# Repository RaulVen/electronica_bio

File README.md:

# electronica_bio
bioreactor_V1

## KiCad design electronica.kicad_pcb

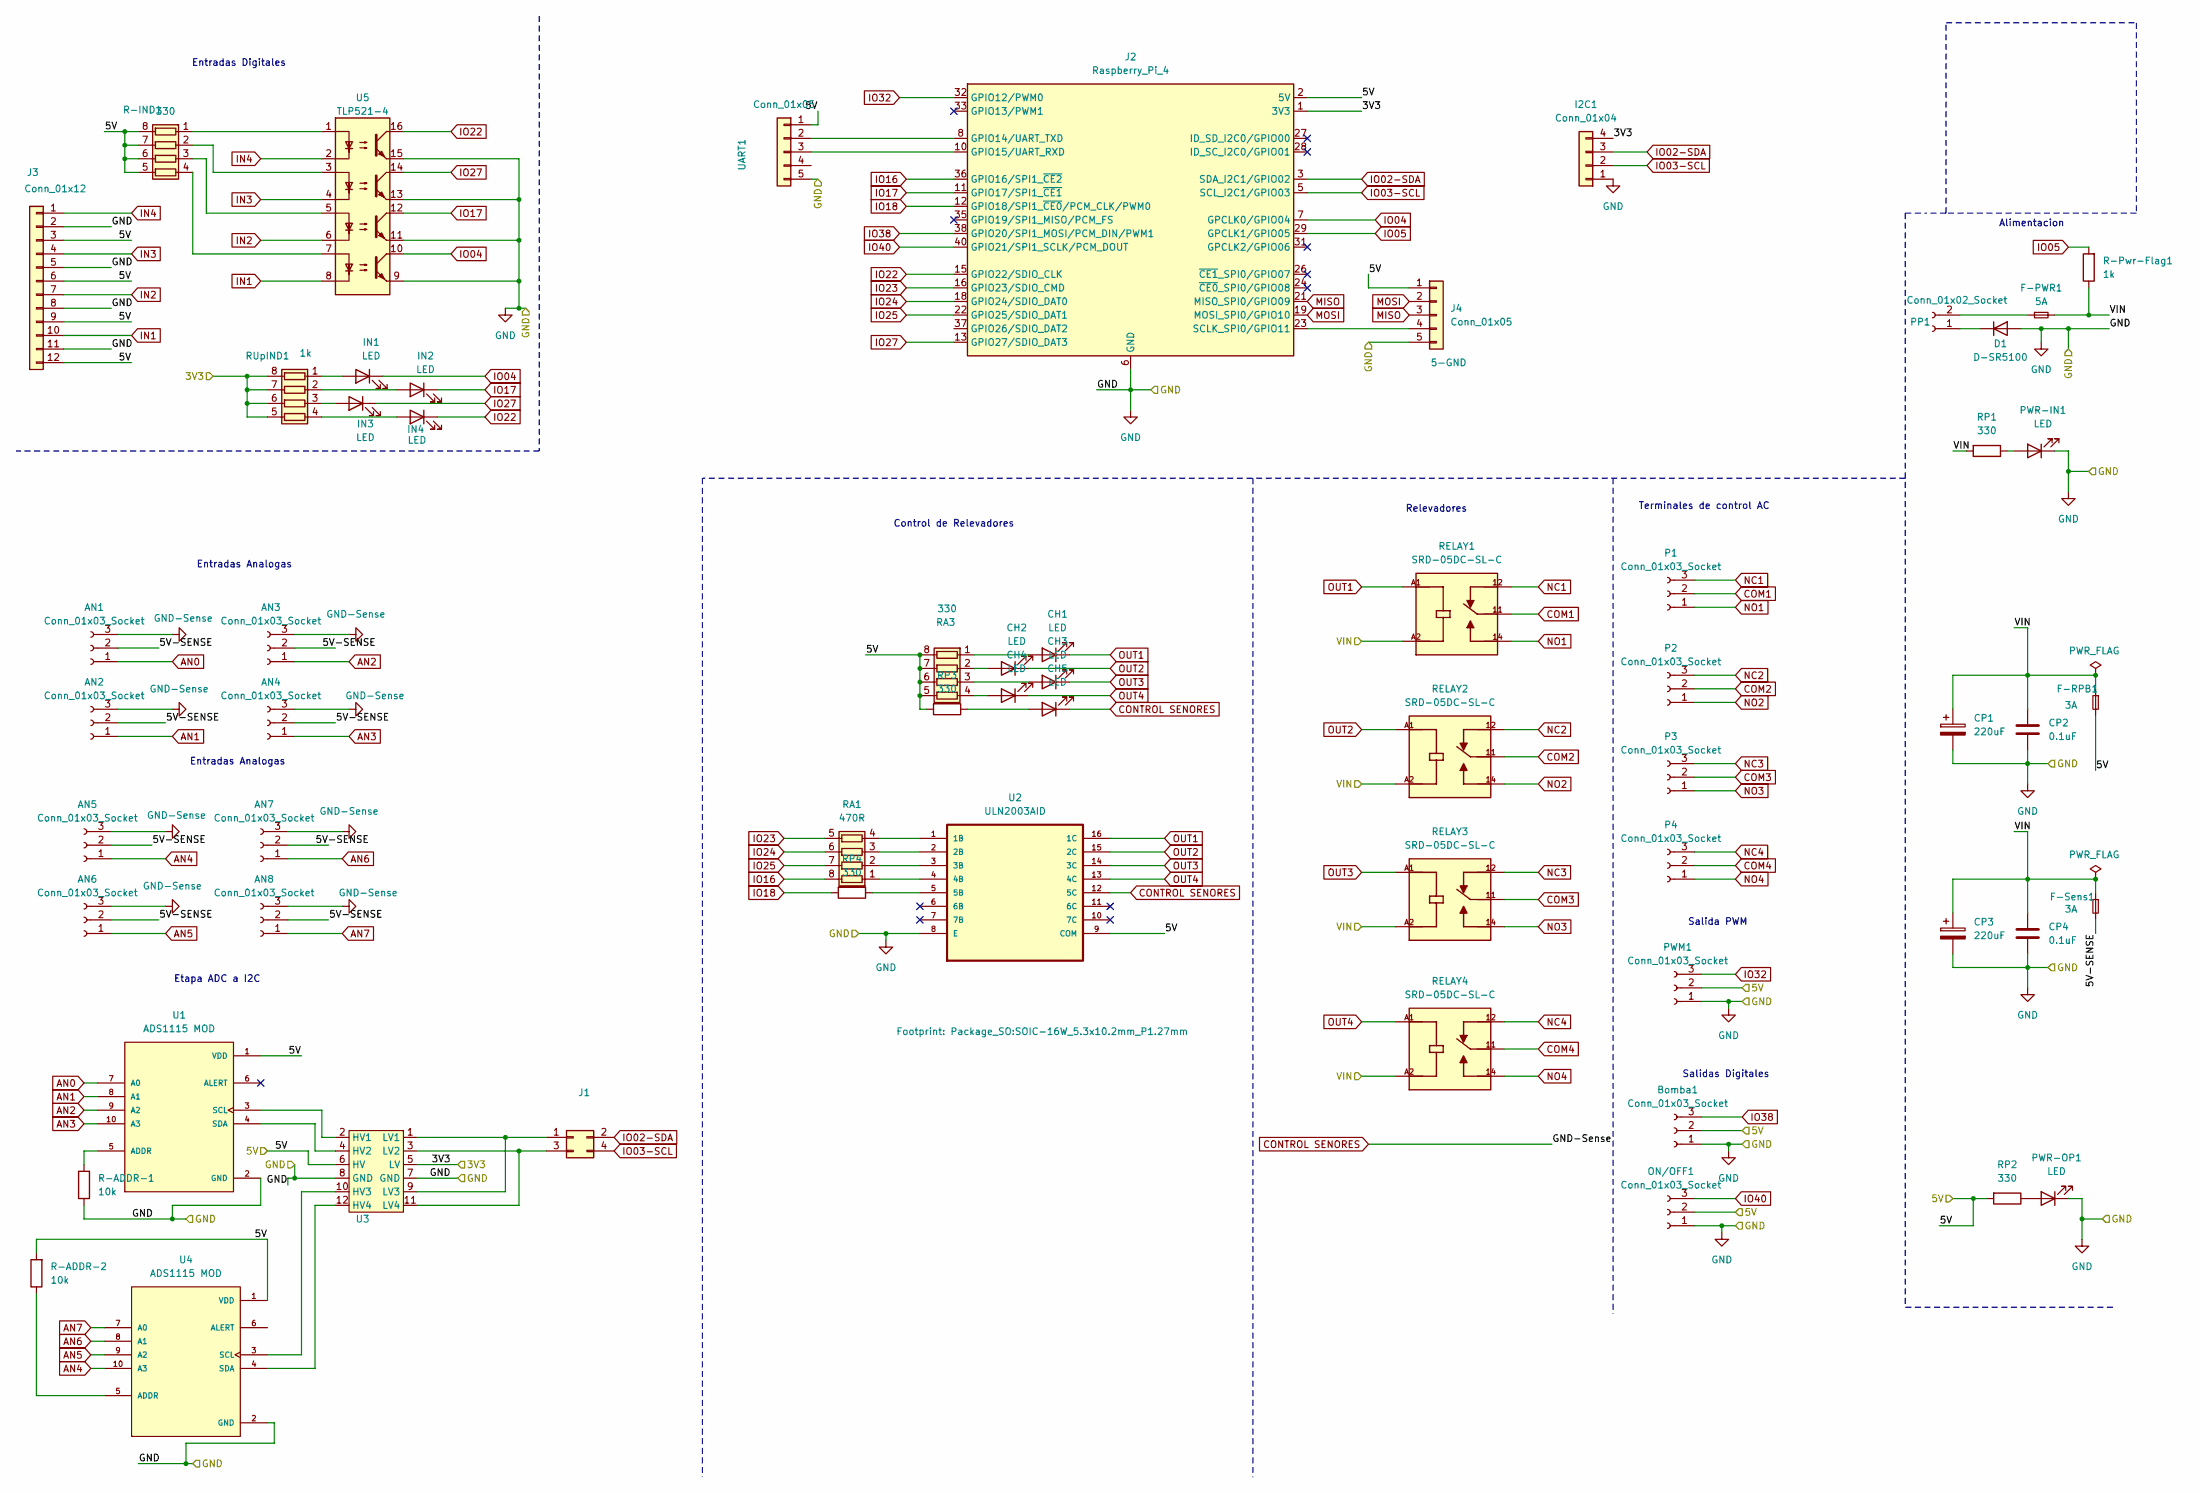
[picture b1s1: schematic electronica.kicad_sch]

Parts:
AN1, AN2, AN3, AN4, AN5, AN6, AN7, AN8: Conn_01x03_Socket; PinHeader_1x03_P2.54mm_Vertical
Bomba1: Conn_01x03_Socket; PinHeader_1x03_P2.54mm_Vertical
CH1, CH2, CH3, CH4, CH5: LED; LED_1206_3216Metric_Pad1.42x1.75mm_HandSolder
CP1, CP3: 220uF; CP_Radial_D8.0mm_P3.50mm
CP2, CP4: 0.1uF; C_1206_3216Metric
D1: D-SR5100; D_DO-41_SOD81_P7.62mm_Horizontal
F-PWR1: 5A; Fuse_1206_3216Metric
F-RPB1: 3A; Fuse_0603_1608Metric
F-Sens1: 3A; Fuse_0603_1608Metric
I2C1: Conn_01x04; PinHeader_1x04_P2.00mm_Vertical
IN1, IN2, IN3, IN4: LED; LED_1206_3216Metric_Pad1.42x1.75mm_HandSolder
J1: Conn_02x02_Counter_Clockwise; PinHeader_2x02_P2.54mm_Vertical
J2: Raspberry_Pi_4; Raspberry4-holes
J3: Conn_01x12; Samtec_HPM-12-05-x-S_Straight_1x12_Pitch5.08mm
J4: Conn_01x05; PinHeader_1x05_P2.00mm_Vertical
ON/OFF1: Conn_01x03_Socket; PinHeader_1x03_P2.54mm_Vertical
P1, P2, P3, P4: Conn_01x03_Socket; TerminalBlock_Phoenix_MKDS-1,5-3_1x03_P5.00mm_Horizontal
PP1: Conn_01x02_Socket; TerminalBlock_Phoenix_MKDS-1,5-2_1x02_P5.00mm_Horizontal
PWM1: Conn_01x03_Socket; PinHeader_1x03_P2.54mm_Vertical
PWR-IN1: LED; LED_1206_3216Metric_Pad1.42x1.75mm_HandSolder
PWR-OP1: LED; LED_1206_3216Metric_Pad1.42x1.75mm_HandSolder
R-ADDR-1, R-ADDR-2: 10k; R_1206_3216Metric_Pad1.30x1.75mm_HandSolder
R-IND1: 330; R_Array_Convex_4x1206
R-Pwr-Flag1: 1k; R_1206_3216Metric_Pad1.30x1.75mm_HandSolder
RA1: 470R; R_Array_Convex_4x1206
RA3: 330; R_Array_Convex_4x1206
RELAY1, RELAY2, RELAY3, RELAY4: SRD-05DC-SL-C; Relay_SPDT_Finder_36.11; PARTREV 1.0
RP1, RP2, RP3, RP4: 330; R_1206_3216Metric_Pad1.30x1.75mm_HandSolder
RUpIND1: 1k; R_Array_Convex_4x1206
U1, U4: ADS1115 MOD; ADS1115; PARTREV NA
U2: ULN2003AID; SOIC-16W_5.3x10.2mm_P1.27mm
U3: LVL Shifter
U5: TLP521-4; SOIC-16_4.55x10.3mm_P1.27mm
UART1: Conn_01x05; PinHeader_1x05_P2.00mm_Vertical

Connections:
/3V3: I2C1.4, J2.1 (3V3), J2.17 (3V3), RUpIND1.5 (R4.2), RUpIND1.6 (R3.2), RUpIND1.7 (R2.2), RUpIND1.8 (R1.2), U3.5 (LV)
/5V: Bomba1.2, F-RPB1.2, J2.2 (5V), J2.4 (5V), J3.3, J3.6, J3.9, J3.12, J4.1, ON/OFF1.2, PWM1.2, R-ADDR-2.2, R-IND1.5 (R4.2), R-IND1.6 (R3.2), R-IND1.7 (R2.2), R-IND1.8 (R1.2), RA3.5 (R4.2), RA3.6 (R3.2), RA3.7 (R2.2), RA3.8 (R1.2), RP2.2, RP3.2, U1.1 (VDD), U2.9 (COM), U3.6 (HV), U4.1 (VDD), UART1.1
/5V-SENSE: AN1.2, AN2.2, AN3.2, AN4.2, AN5.2, AN6.2, AN7.2, AN8.2, F-Sens1.2
/VIN: CP1.1, CP2.1, CP3.1, CP4.1, F-PWR1.2, F-RPB1.1, F-Sens1.1, R-Pwr-Flag1.1, RELAY1.A2, RELAY2.A2, RELAY3.A2, RELAY4.A2, RP1.2
AN0: AN1.1, U1.7 (A0)
AN1: AN2.1, U1.8 (A1)
AN2: AN3.1, U1.9 (A2)
AN3: AN4.1, U1.10 (A3)
AN4: AN5.1, U4.10 (A3)
AN5: AN6.1, U4.9 (A2)
AN6: AN7.1, U4.8 (A1)
AN7: AN8.1, U4.7 (A0)
COM1: P1.2, RELAY1.11
COM2: P2.2, RELAY2.11
COM3: P3.2, RELAY3.11
COM4: P4.2, RELAY4.11
CONTROL SENORES: AN1.3, AN2.3, AN3.3, AN4.3, AN5.3, AN6.3, AN7.3, AN8.3, CH5.1 (K), U2.12 (5C)
GND: Bomba1.1, CP1.2, CP2.2, CP3.2, CP4.2, D1.2 (A), I2C1.1, J2.6 (GND), J2.9 (GND), J2.14 (GND), J2.20 (GND), J2.25 (GND), J2.30 (GND), J2.34 (GND), J2.39 (GND), J3.2, J3.5, J3.8, J3.11, J4.5, ON/OFF1.1, PWM1.1, PWR-IN1.1 (K), PWR-OP1.1 (K), R-ADDR-1.1, U1.2 (GND), U2.8 (E), U3.7 (GND), U3.8 (GND), U4.2 (GND), U5.9, U5.11, U5.13, U5.15, UART1.5
IN1: J3.10, U5.8
IN2: J3.7, U5.6
IN3: J3.4, U5.4
IN4: J3.1, U5.2
IO02-SDA: I2C1.3, J1.2 (Pin_4), J2.3 (SDA_I2C1/GPIO02)
IO03-SCL: I2C1.2, J1.4 (Pin_3), J2.5 (SCL_I2C1/GPIO03)
IO04: IN1.1 (K), J2.7 (GPCLK0/GPIO04), U5.10
IO05: J2.29 (GPCLK1/GPIO05), R-Pwr-Flag1.2
IO16: J2.36 (GPIO16/SPI1_~CE2), RA1.8 (R1.2)
IO17: IN2.1 (K), J2.11 (GPIO17/SPI1_~CE1), U5.12
IO18: J2.12 (GPIO18/SPI1_~CE0/PCM_CLK/PWM0), RP4.2
IO22: IN4.1 (K), J2.15 (GPIO22/SDIO_CLK), U5.16
IO23: J2.16 (GPIO23/SDIO_CMD), RA1.5 (R4.2)
IO24: J2.18 (GPIO24/SDIO_DAT0), RA1.6 (R3.2)
IO25: J2.22 (GPIO25/SDIO_DAT1), RA1.7 (R2.2)
IO27: IN3.1 (K), J2.13 (GPIO27/SDIO_DAT3), U5.14
IO32: J2.32 (GPIO12/PWM0), PWM1.3
IO38: Bomba1.3, J2.38 (GPIO20/SPI1_MOSI/PCM_DIN/PWM1)
IO40: J2.40 (GPIO21/SPI1_SCLK/PCM_DOUT), ON/OFF1.3
MISO: J2.21 (MISO_SPI0/GPIO09), J4.3
MOSI: J2.19 (MOSI_SPI0/GPIO10), J4.2
NC1: P1.3, RELAY1.12
NC2: P2.3, RELAY2.12
NC3: P3.3, RELAY3.12
NC4: P4.3, RELAY4.12
NO1: P1.1, RELAY1.14
NO2: P2.1, RELAY2.14
NO3: P3.1, RELAY3.14
NO4: P4.1, RELAY4.14
unnamed: CH1.2 (A), RA3.1 (R1.1)
unnamed: CH2.2 (A), RA3.2 (R2.1)
unnamed: CH3.2 (A), RA3.3 (R3.1)
unnamed: CH4.2 (A), RA3.4 (R4.1)
unnamed: CH5.2 (A), RP3.1
unnamed: D1.1 (K), PP1.1
unnamed: IN1.2 (A), RUpIND1.1 (R1.1)
unnamed: IN2.2 (A), RUpIND1.2 (R2.1)
unnamed: IN3.2 (A), RUpIND1.3 (R3.1)
unnamed: IN4.2 (A), RUpIND1.4 (R4.1)
unnamed: J1.1, U3.1 (LV1), U3.9 (LV3)
unnamed: J1.3 (Pin_2), U3.3 (LV2), U3.11 (LV4)
unnamed: J2.8 (GPIO14/UART_TXD), UART1.2
unnamed: J2.10 (GPIO15/UART_RXD), UART1.3
unnamed: J2.23 (SCLK_SPI0/GPIO11), J4.4
unnamed: F-PWR1.1, PP1.2
unnamed: PWR-IN1.2 (A), RP1.1
unnamed: PWR-OP1.2 (A), RP2.1
unnamed: R-IND1.1 (R1.1), U5.1
unnamed: R-IND1.2 (R2.1), U5.3
unnamed: R-IND1.3 (R3.1), U5.5
unnamed: R-IND1.4 (R4.1), U5.7
unnamed: RA1.1 (R1.1), U2.4 (4B)
unnamed: RA1.2 (R2.1), U2.3 (3B)
unnamed: RA1.3 (R3.1), U2.2 (2B)
unnamed: RA1.4 (R4.1), U2.1 (1B)
unnamed: R-ADDR-1.2, U1.5 (ADDR)
unnamed: U1.3 (SCL), U3.2 (HV1)
unnamed: U1.4 (SDA), U3.4 (HV2)
unnamed: RP4.1, U2.5 (5B)
unnamed: U3.10 (HV3), U4.3 (SCL)
unnamed: U3.12 (HV4), U4.4 (SDA)
unnamed: R-ADDR-2.1, U4.5 (ADDR)
OUT1: CH1.1 (K), RELAY1.A1, U2.16 (1C)
OUT2: CH2.1 (K), RELAY2.A1, U2.15 (2C)
OUT3: CH3.1 (K), RELAY3.A1, U2.14 (3C)
OUT4: CH4.1 (K), RELAY4.A1, U2.13 (4C)

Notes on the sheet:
Entradas Analogas
Alimentacion
Relevadores
Salidas Digitales
Terminales de control AC
Entradas Digitales
Control de Relevadores
Etapa ADC a I2C
Salida PWM

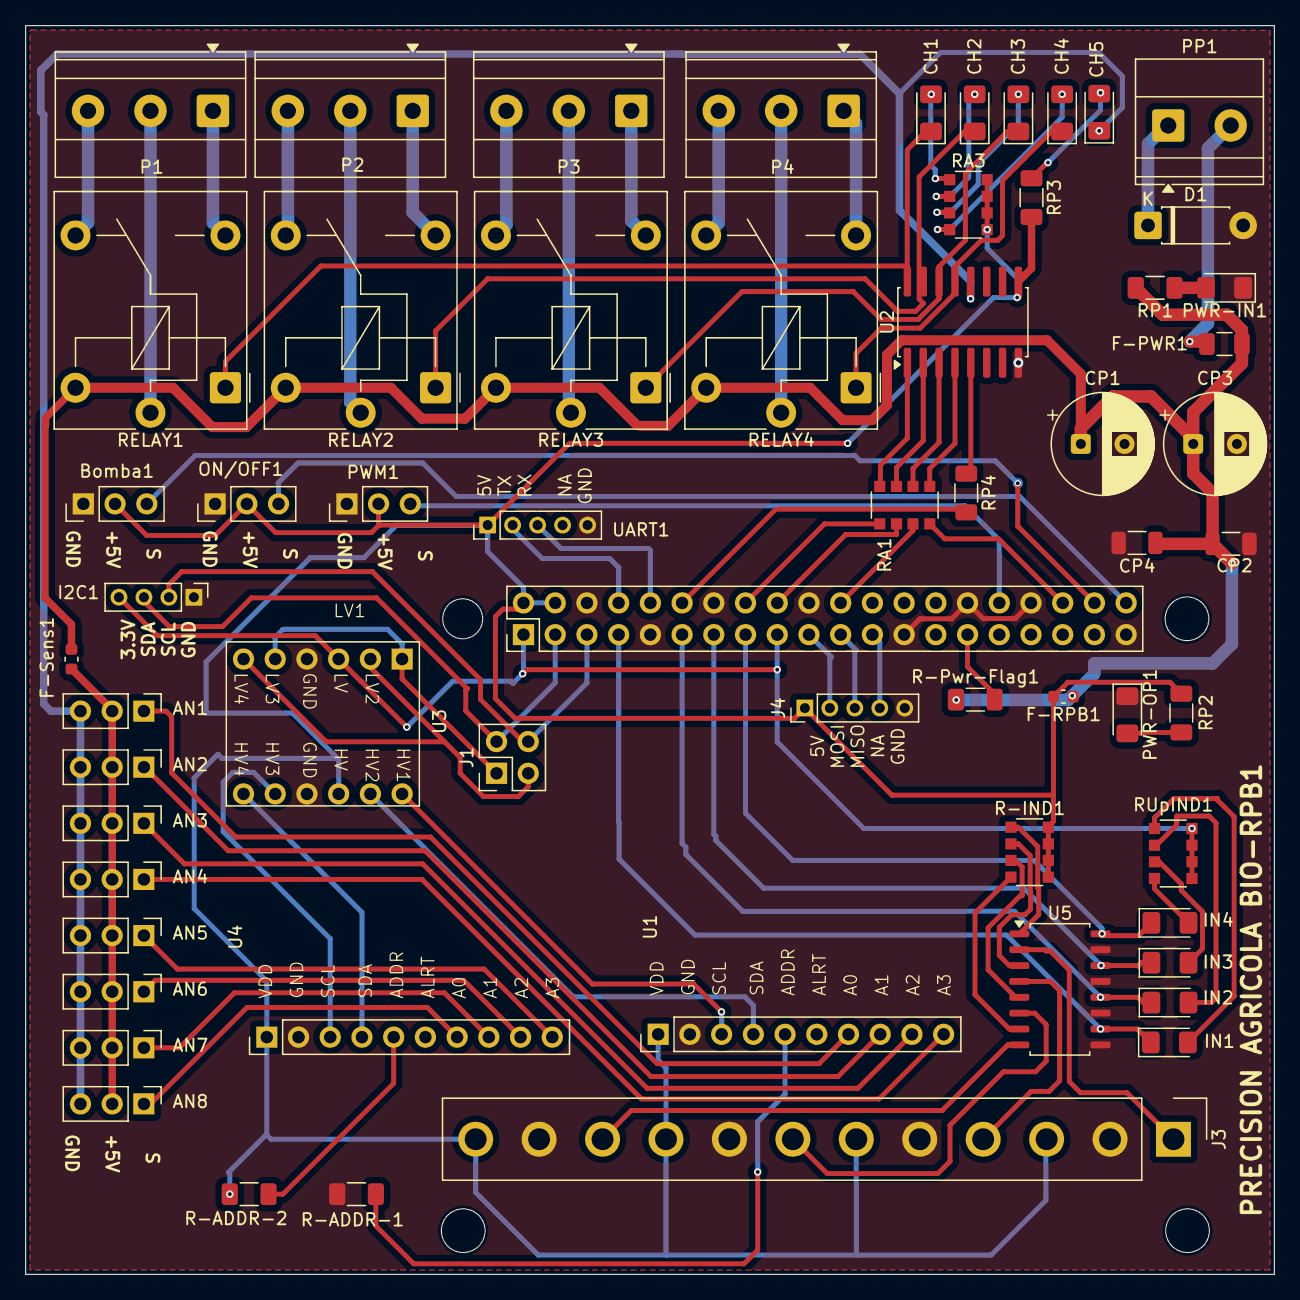
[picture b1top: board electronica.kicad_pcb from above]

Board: 2 copper layers, 100.0 x 100.0 mm, 61 parts (0 on the bottom side), 84 nets.

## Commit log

2025-10-28 Version inicial biorector
2025-10-28 en el esquematico coloque el brakeout del shifter, genere las librerias y simbolos, modifique los sensores que trabaja a 3.3 en el esquematico
2025-10-29 agrege los foodprints de rtc, y shifter al pcb en general, agrege un par de pistas a los i2c de 3.3, los que trabajan a 5v los deje como sda-h y sclh
2025-10-31 feat: integrated rtc ldc i2c / fixed 12v power line rs485 / output com pin -> input power type
2025-11-05 draft:updating pcb dimentions
2025-11-05 feat: position of the components improved
2025-11-06 Reinicio del repositorio tras corrupción de HEAD
2025-11-07 ya quedo las lineas del pcb
2025-11-07 ya tiene las borneras faltantes
2025-11-13 feat: final review
2025-11-14 feat: final quick fixes
2025-12-03 tarjeta para raspberri, pdfs y relacion de pines
2025-12-03 relacion de gpios, inicio de esquematico-salidas en proceso
2025-12-10 en proceso de hacer el diseño, coloque el modulo de adc a i2c por que es mas barato que comprar las piezas
2025-12-23 test: check pushing permits on Lalo user by adding a test.txt empty file
2025-12-26 tarjeta terminada para revisión
2025-12-27 conecciones corregidas
2025-12-27 permanece un warning pero no deberia dar problemas4
2025-12-30 actualizacion de la tarjeta, integracion de otro modulo ads1115 para leer 8 sensores analogos en total e integracion de un ci de opto acopladores de 5 salidas
2025-12-30 zona de gnds
2025-12-30 solo 1 error
2025-12-30 agrege un conector de i2C a3.3v por lo que se ofresca
2026-01-03 movi las vias y optimice algunas rutas
